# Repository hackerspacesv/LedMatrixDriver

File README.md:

# LedMatrixDriver
LED Matrix Driver for the Lattice ICE40 FPGA

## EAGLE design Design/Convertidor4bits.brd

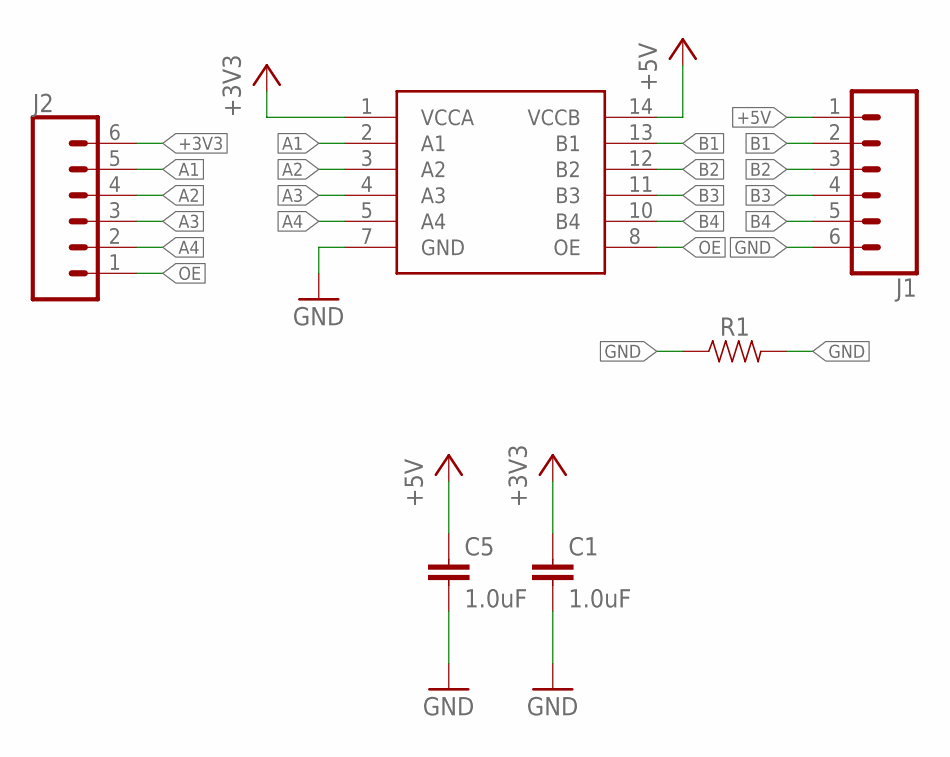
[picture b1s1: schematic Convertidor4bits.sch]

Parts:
C1, C5: 1.0uF; 0805
IC1: TXB0104; SO14
J1, J2: CONN_06LONGPADS; 1X06_LONGPADS
R1: 0805

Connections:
+3V3: C1.1, IC1.1 (VCCA), J2.6
+5V: C5.1, IC1.14 (VCCB), J1.1
A1: IC1.2 (A1), J2.5
A2: IC1.3 (A2), J2.4
A3: IC1.4 (A3), J2.3
A4: IC1.5 (A4), J2.2
B1: IC1.13 (B1), J1.2
B2: IC1.12 (B2), J1.3
B3: IC1.11 (B3), J1.4
B4: IC1.10 (B4), J1.5
GND: C1.2, C5.2, IC1.7 (GND), J1.6, R1.1, R1.2
OE: IC1.8 (OE), J2.1

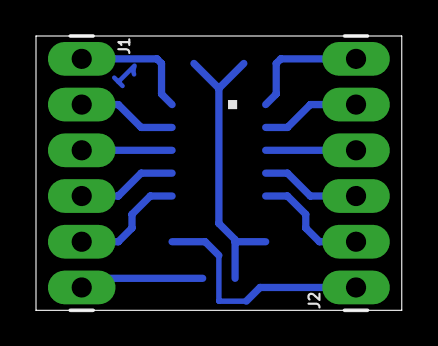
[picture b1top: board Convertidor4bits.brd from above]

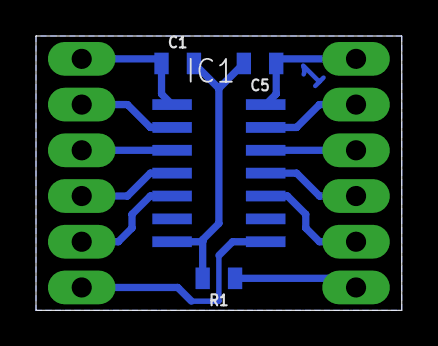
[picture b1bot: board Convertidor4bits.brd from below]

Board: 2 copper layers, 20.3 x 15.2 mm, 6 parts (4 on the bottom side), 12 nets.

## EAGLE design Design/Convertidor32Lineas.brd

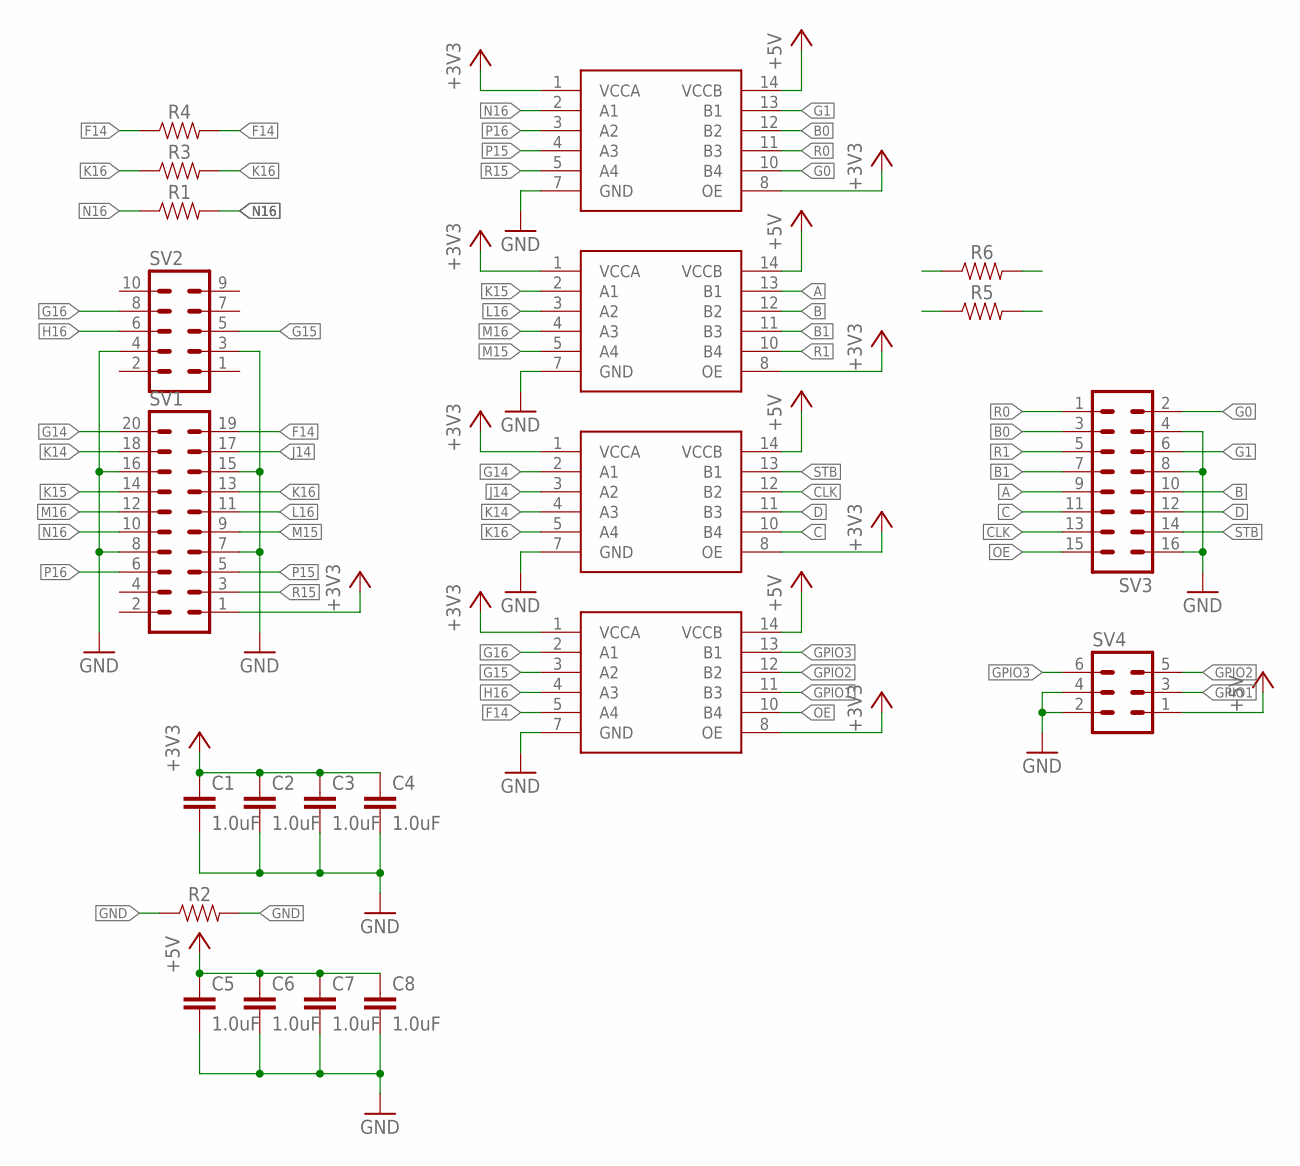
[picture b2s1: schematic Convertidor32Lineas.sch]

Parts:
C1, C2, C3, C4, C5, C6, C7, C8: 1.0uF; 0805
IC1, IC2, IC3, IC4: TXB0104; SO14
R1, R2, R3, R4, R5, R6: 0805
SV1: MA10-2
SV2: MA05-2
SV3: MA08-2
SV4: MA03-2

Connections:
+3V3: C1.1, C2.1, C3.1, C4.1, IC1.1 (VCCA), IC1.8 (OE), IC2.1 (VCCA), IC2.8 (OE), IC3.1 (VCCA), IC3.8 (OE), IC4.1 (VCCA), IC4.8 (OE), SV1.1
+5V: C5.1, C6.1, C7.1, C8.1, IC1.14 (VCCB), IC2.14 (VCCB), IC3.14 (VCCB), IC4.14 (VCCB), SV4.1
A: IC2.13 (B1), SV3.9
B: IC2.12 (B2), SV3.10
B0: IC1.12 (B2), SV3.3
B1: IC2.11 (B3), SV3.7
C: IC3.10 (B4), SV3.11
CLK: IC3.12 (B2), SV3.13
D: IC3.11 (B3), SV3.12
F14: IC4.5 (A4), R4.1, R4.2, SV1.19
G0: IC1.10 (B4), SV3.2
G1: IC1.13 (B1), SV3.6
G14: IC3.2 (A1), SV1.20
G15: IC4.3 (A2), SV2.5
G16: IC4.2 (A1), SV2.8
GND: C1.2, C2.2, C3.2, C4.2, C5.2, C6.2, C7.2, C8.2, IC1.7 (GND), IC2.7 (GND), IC3.7 (GND), IC4.7 (GND), R2.1, R2.2, SV1.7, SV1.8, SV1.15, SV1.16, SV2.3, SV2.4, SV3.4, SV3.8, SV3.16, SV4.2, SV4.4
GPIO1: IC4.11 (B3), SV4.3
GPIO2: IC4.12 (B2), SV4.5
GPIO3: IC4.13 (B1), SV4.6
H16: IC4.4 (A3), SV2.6
J14: IC3.3 (A2), SV1.17
K14: IC3.4 (A3), SV1.18
K15: IC2.2 (A1), SV1.14
K16: IC3.5 (A4), R3.1, R3.2, SV1.13
L16: IC2.3 (A2), SV1.11
M15: IC2.5 (A4), SV1.9
M16: IC2.4 (A3), SV1.12
N16: IC1.2 (A1), R1.1, R1.2, SV1.10
OE: IC4.10 (B4), R6.1, R6.2, SV3.15
P15: IC1.4 (A3), SV1.5
P16: IC1.3 (A2), SV1.6
R0: IC1.11 (B3), SV3.1
R1: IC2.10 (B4), R5.1, R5.2, SV3.5
R15: IC1.5 (A4), SV1.3
STB: IC3.13 (B1), SV3.14

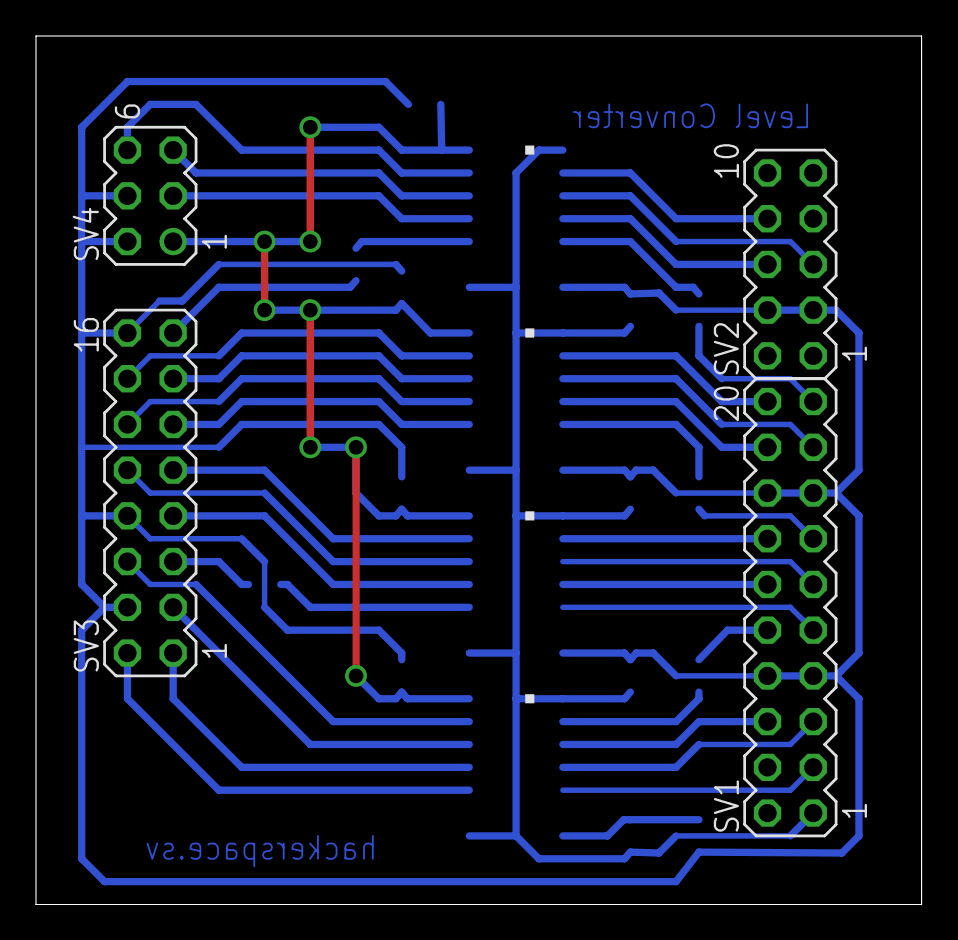
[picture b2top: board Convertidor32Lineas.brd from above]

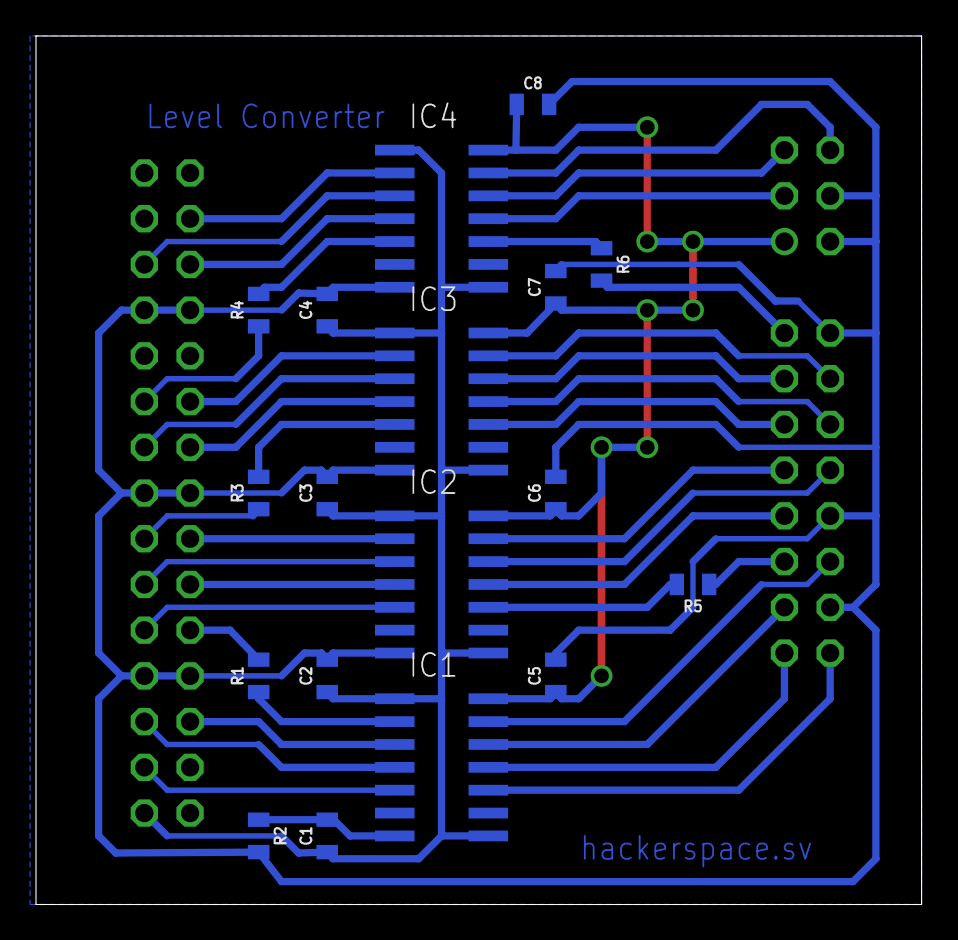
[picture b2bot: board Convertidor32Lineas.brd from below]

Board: 2 copper layers, 49.2 x 48.2 mm, 22 parts (18 on the bottom side), 35 nets.

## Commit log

2018-02-12 Initial commit: Makefile template and simple tests.
2018-02-12 Agregada generacion de clock y LEDs de monitoreo.
2018-02-13 Agregados pines de matriz de LED
2018-02-14 Testing new logic drive.
2018-02-14 Right signals but noisy output. Check with osciloscope.
2018-02-15 Added working example with test pattern.
2018-02-28 Pruebas de acceso a memoria
2018-03-01 Agregada prueba de NyanCat
2018-03-02 Agregadas notas de Copyright y comentarios.
2018-04-13 Added level converter design
2018-04-16 Added support for voltage level converter

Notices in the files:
parts and their libraries:
SparkFun-Resistors: Licensing: Creative Commons ShareAlike 4.0 International - https://creativecommons.org/licenses/by-sa/4.0
